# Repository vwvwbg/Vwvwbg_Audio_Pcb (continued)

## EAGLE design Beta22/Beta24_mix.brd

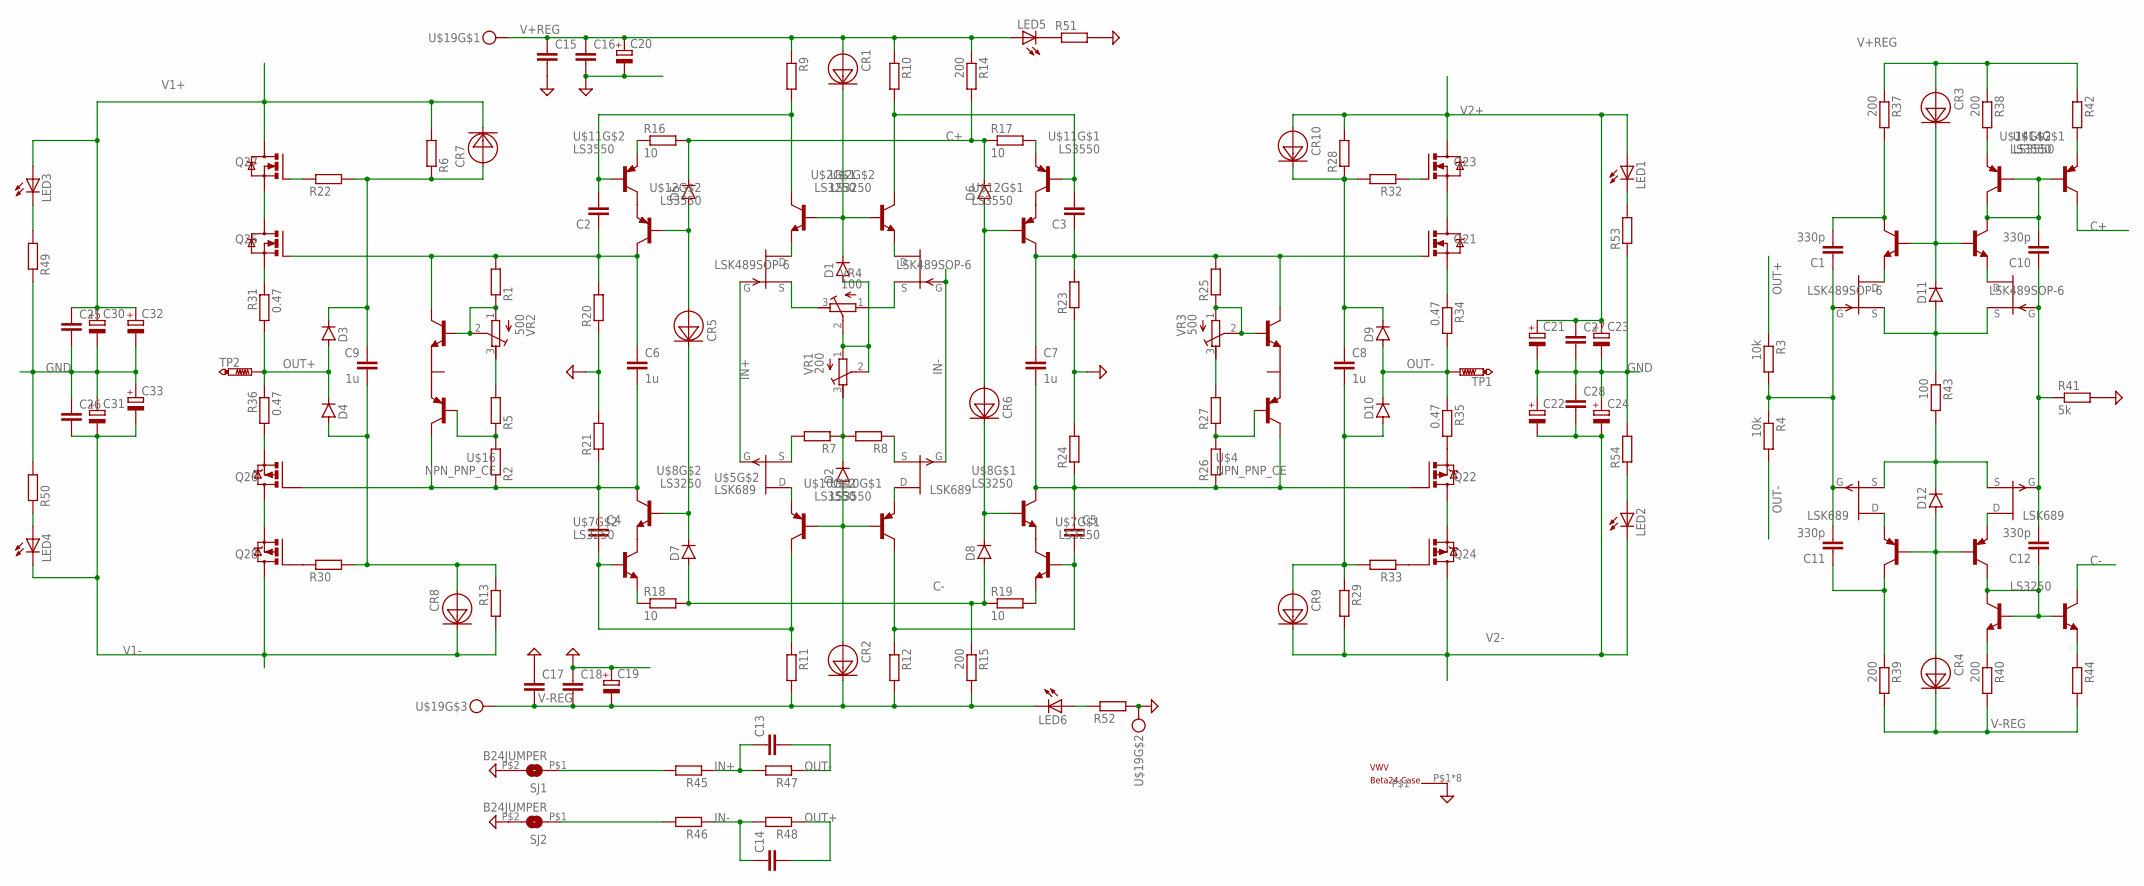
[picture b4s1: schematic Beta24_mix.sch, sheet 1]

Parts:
C1, C10, C11, C12: 330p; C1206
C2, C3, C4, C5, C13, C14, C15, C16, C17, C18, C25, C26, C27, C28: C-EUC1206; C1206
C6, C7: 1u; C1210
C8, C9: 1u; C1206
C19, C20, C21, C22, C23, C24, C30, C31, C32, C33: CPOL-EUG; PANASONIC_G
CR1, CR2, CR3, CR4, CR5, CR6, CR7, CR8, CR9, CR10: 1N5283; SMD
D1, D2, D3, D4, D5, D6, D7, D8, D9, D10, D11, D12: DIODE-SOD80C; SOD80C
LED1, LED2, LED3, LED4, LED5, LED6: LED_LEDSML1206; LED_SML1206
Q21, Q23, Q25, Q27: IRFZ24ND2PAK; TO254P1054X240-3M
Q22, Q24, Q26, Q28: IRF9Z34D2PAK; TO254P1054X240-3M
R1, R2, R5, R6, R7, R8, R9, R10, R11, R12, R13, R20, R21, R22, R23, R24, R25, R26, R27, R28, R29, R30, R32, R33, R42, R44, R45, R46, R47, R48, R49, R50, R52, R53, R54: R-EU_MELF0204W; MINI_MELF-0204W
R3, R4: 10k; MINI_MELF-0204W
R14, R15, R37, R38, R39, R40, R51: 200; MINI_MELF-0204W
R16, R17, R18, R19: 10; MINI_MELF-0204W
R31, R34, R35, R36: 0.47; R2512
R41: 5k; MINI_MELF-0204W
R43: 100; MINI_MELF-0204W
SJ1, SJ2: B24JUMPER; B24J
TP1, TP2: PTR1PAD1-20; P1-20
U$1, U$3: LSK489SOP-6; SOT-23-6
U$2, U$6, U$7, U$8, U$13: LS3250; SOT-23-6
U$4, U$16: NPN_PNP_CE; SOT25
U$5, U$15: LSK689; SOT-23-6
U$9, U$10, U$11, U$12, U$14: LS3550; SOT-23-6
U$17: VWV
U$18: B24C
U$19: CON-PTSM-3
VR1: 200; RTRIM3296W
VR2, VR3: 500; RTRIM3296W
VR4: 100; RTRIM3296W

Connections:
C+: D5.C, D6.C, R14.2, R16.2, R17.1, U$14.6 (C)
C-: D7.A, D8.A, R15.1, R18.2, R19.1, U$13.6 (C)
GND: C15.2, C16.2, C17.1, C18.1, C19.+, C20.-, C21.-, C22.+, C23.-, C24.+, C25.2, C26.1, C27.2, C28.1, C30.-, C31.+, C32.-, C33.+, R20.1, R21.2, R23.1, R24.2, R41.2, R49.1, R50.2, R51.2, R52.2, R53.1, R54.2, SJ1.P$2 (2), SJ2.P$2 (2), U$18.P$1, U$18.P$2, U$18.P$3, U$18.P$4, U$18.P$5, U$18.P$6, U$18.P$7, U$18.P$8, U$19.P$4; also elsewhere on the board
IN+: C13.1, R45.1, R47.2, U$1.1 (G), U$5.4 (G)
IN-: C14.1, R46.1, R48.2, U$1.4 (G), U$5.1 (G)
unnamed: C12.1, U$9.6 (C), U$13.1 (B), U$13.3 (B), U$13.4 (C)
unnamed: U$1.5 (D), U$2.2 (E)
unnamed: U$1.3 (S), VR4.3 (E)
unnamed: R7.2, U$5.6 (S)
unnamed: U$1.2 (D), U$2.5 (E)
unnamed: U$5.5 (D), U$10.2 (E)
unnamed: U$1.6 (S), VR4.1 (A)
unnamed: D2.C, R7.1, R8.2, VR1.3 (E)
unnamed: R8.1, U$5.3 (S)
unnamed: U$5.2 (D), U$10.5 (E)
unnamed: D1.A, VR1.1 (A), VR1.2 (S), VR4.2 (S)
unnamed: CR2.ANODE, D2.A, U$10.1 (B), U$10.3 (B)
unnamed: C2.2, R9.2, U$2.6 (C), U$11.3 (B)
unnamed: C3.2, R10.2, U$2.4 (C), U$11.1 (B)
unnamed: C3.1, C7.1, Q21.1 (G), R23.2, R25.2, U$4.5 (C1), U$12.6 (C)
unnamed: CR1.CATHODE, D1.C, U$2.1 (B), U$2.3 (B)
unnamed: R40.1, U$13.2 (E)
unnamed: C5.2, R12.1, U$7.1 (B), U$10.6 (C)
unnamed: C1.1, C11.2, R3.2, R4.1, U$3.1 (G), U$15.4 (G)
unnamed: C8.2, CR9.ANODE, D10.A, R29.1, R33.2
unnamed: D12.C, R43.2, U$15.3 (S), U$15.6 (S)
unnamed: D11.A, R43.1, U$3.3 (S), U$3.6 (S)
unnamed: U$11.6 (C), U$12.5 (E)
unnamed: C4.2, R11.1, U$7.3 (B), U$10.4 (C)
unnamed: U$11.4 (C), U$12.2 (E)
unnamed: R38.2, U$14.2 (E)
unnamed: R16.1, U$11.2 (E)
unnamed: R17.2, U$11.5 (E)
unnamed: C10.2, U$6.4 (C), U$14.1 (B), U$14.3 (B), U$14.4 (C)
unnamed: R18.1, U$7.2 (E)
unnamed: R19.2, U$7.5 (E)
unnamed: R45.2, SJ1.P$1 (1)
unnamed: U$3.5 (D), U$6.2 (E)
unnamed: CR4.ANODE, D12.A, U$9.1 (B), U$9.3 (B)
unnamed: C2.1, C6.1, Q25.1 (G), R1.2, R20.2, U$12.4 (C), U$16.5 (C1)
unnamed: C4.1, C6.2, Q26.1 (G), R2.1, R21.1, U$8.4 (C), U$16.4 (C2)
unnamed: U$7.6 (C), U$8.5 (E)
unnamed: U$7.4 (C), U$8.2 (E)
unnamed: R25.1, U$4.1 (B1), VR3.1 (A), VR3.2 (S)
unnamed: C1.2, R37.2, U$6.6 (C)
unnamed: CR5.ANODE, D5.A, U$12.3 (B)
unnamed: CR6.ANODE, D6.A, U$12.1 (B)
unnamed: CR5.CATHODE, D7.C, U$8.3 (B)
unnamed: CR6.CATHODE, D8.C, U$8.1 (B)
unnamed: R26.2, R27.1, U$4.3 (B2)
unnamed: R27.2, VR3.3 (E)
unnamed: C5.1, C7.2, Q22.1 (G), R24.1, R26.1, U$4.4 (C2), U$8.6 (C)
unnamed: R2.2, R5.1, U$16.3 (B2)
unnamed: R44.1, U$13.5 (E)
unnamed: C8.1, CR10.CATHODE, D9.C, R28.1, R32.2
unnamed: Q21.2 (D), Q21.4 (D), Q21.P$1 (D), Q21.P$2 (D), Q21.P$3 (D), Q21.P$4 (D), Q21.P$5 (D), Q21.P$6 (D), Q21.P$7 (D), Q21.P$8 (D), Q21.P$9 (D), Q21.P$10 (D), Q21.P$11 (D), Q21.P$12 (D), Q21.P$13 (D), Q21.P$14 (D), Q21.P$15 (D), Q21.P$16 (D), Q21.P$17 (D), Q21.P$18 (D), Q21.P$19 (D), Q21.P$20 (D), Q21.P$21 (D), Q21.P$22 (D), Q21.P$23 (D), Q21.P$24 (D), Q21.P$25 (D), Q21.P$26 (D), Q21.P$27 (D), Q21.P$28 (D), Q21.P$29 (D), Q21.P$30 (D), Q21.P$31 (D), Q21.P$32 (D), Q21.P$33 (D), Q21.P$34 (D), Q21.P$35 (D), Q21.P$36 (D), Q21.P$37 (D), Q21.P$38 (D), Q21.P$39 (D), Q21.P$40 (D), Q21.P$41 (D), Q21.P$42 (D), Q21.P$43 (D), Q21.P$44 (D), Q21.P$45 (D), Q21.P$46 (D), Q21.P$47 (D), Q21.P$48 (D), Q21.P$49 (D), Q21.P$50 (D), Q21.P$51 (D), Q21.P$52 (D), Q21.P$53 (D), Q21.P$54 (D), Q21.P$55 (D), Q21.P$56 (D), Q21.P$57 (D), Q21.P$58 (D), Q21.P$59 (D), Q21.P$60 (D), Q21.P$61 (D), Q21.P$62 (D), Q21.P$63 (D), Q23.3 (S)
unnamed: Q22.2 (D), Q22.4 (D), Q22.P$1 (D), Q22.P$2 (D), Q22.P$3 (D), Q22.P$4 (D), Q22.P$5 (D), Q22.P$6 (D), Q22.P$7 (D), Q22.P$8 (D), Q22.P$9 (D), Q22.P$10 (D), Q22.P$11 (D), Q22.P$12 (D), Q22.P$13 (D), Q22.P$14 (D), Q22.P$15 (D), Q22.P$16 (D), Q22.P$17 (D), Q22.P$18 (D), Q22.P$19 (D), Q22.P$20 (D), Q22.P$21 (D), Q22.P$22 (D), Q22.P$23 (D), Q22.P$24 (D), Q22.P$25 (D), Q22.P$26 (D), Q22.P$27 (D), Q22.P$28 (D), Q22.P$29 (D), Q22.P$30 (D), Q22.P$31 (D), Q22.P$32 (D), Q22.P$33 (D), Q22.P$34 (D), Q22.P$35 (D), Q22.P$36 (D), Q22.P$37 (D), Q22.P$38 (D), Q22.P$39 (D), Q22.P$40 (D), Q22.P$41 (D), Q22.P$42 (D), Q22.P$43 (D), Q22.P$44 (D), Q22.P$45 (D), Q22.P$46 (D), Q22.P$47 (D), Q22.P$48 (D), Q22.P$49 (D), Q22.P$50 (D), Q22.P$51 (D), Q22.P$52 (D), Q22.P$53 (D), Q22.P$54 (D), Q22.P$55 (D), Q22.P$56 (D), Q22.P$57 (D), Q22.P$58 (D), Q22.P$59 (D), Q22.P$60 (D), Q22.P$61 (D), Q22.P$62 (D), Q22.P$63 (D), Q24.3 (S)
unnamed: Q23.1 (G), R32.1
unnamed: Q24.1 (G), R33.1
unnamed: C9.1, CR7.ANODE, D3.C, R6.1, R22.2
unnamed: Q21.3 (S), R34.1
unnamed: Q22.3 (S), R35.2
unnamed: C9.2, CR8.ANODE, D4.A, R13.1, R30.2
unnamed: Q25.2 (D), Q25.4 (D), Q25.P$1 (D), Q25.P$2 (D), Q25.P$3 (D), Q25.P$4 (D), Q25.P$5 (D), Q25.P$6 (D), Q25.P$7 (D), Q25.P$8 (D), Q25.P$9 (D), Q25.P$10 (D), Q25.P$11 (D), Q25.P$12 (D), Q25.P$13 (D), Q25.P$14 (D), Q25.P$15 (D), Q25.P$16 (D), Q25.P$17 (D), Q25.P$18 (D), Q25.P$19 (D), Q25.P$20 (D), Q25.P$21 (D), Q25.P$22 (D), Q25.P$23 (D), Q25.P$24 (D), Q25.P$25 (D), Q25.P$26 (D), Q25.P$27 (D), Q25.P$28 (D), Q25.P$29 (D), Q25.P$30 (D), Q25.P$31 (D), Q25.P$32 (D), Q25.P$33 (D), Q25.P$34 (D), Q25.P$35 (D), Q25.P$36 (D), Q25.P$37 (D), Q25.P$38 (D), Q25.P$39 (D), Q25.P$40 (D), Q25.P$41 (D), Q25.P$42 (D), Q25.P$43 (D), Q25.P$44 (D), Q25.P$45 (D), Q25.P$46 (D), Q25.P$47 (D), Q25.P$48 (D), Q25.P$49 (D), Q25.P$50 (D), Q25.P$51 (D), Q25.P$52 (D), Q25.P$53 (D), Q25.P$54 (D), Q25.P$55 (D), Q25.P$56 (D), Q25.P$57 (D), Q25.P$58 (D), Q25.P$59 (D), Q25.P$60 (D), Q25.P$61 (D), Q25.P$62 (D), Q25.P$63 (D), Q27.3 (S)
unnamed: Q26.2 (D), Q26.4 (D), Q26.P$1 (D), Q26.P$2 (D), Q26.P$3 (D), Q26.P$4 (D), Q26.P$5 (D), Q26.P$6 (D), Q26.P$7 (D), Q26.P$8 (D), Q26.P$9 (D), Q26.P$10 (D), Q26.P$11 (D), Q26.P$12 (D), Q26.P$13 (D), Q26.P$14 (D), Q26.P$15 (D), Q26.P$16 (D), Q26.P$17 (D), Q26.P$18 (D), Q26.P$19 (D), Q26.P$20 (D), Q26.P$21 (D), Q26.P$22 (D), Q26.P$23 (D), Q26.P$24 (D), Q26.P$25 (D), Q26.P$26 (D), Q26.P$27 (D), Q26.P$28 (D), Q26.P$29 (D), Q26.P$30 (D), Q26.P$31 (D), Q26.P$32 (D), Q26.P$33 (D), Q26.P$34 (D), Q26.P$35 (D), Q26.P$36 (D), Q26.P$37 (D), Q26.P$38 (D), Q26.P$39 (D), Q26.P$40 (D), Q26.P$41 (D), Q26.P$42 (D), Q26.P$43 (D), Q26.P$44 (D), Q26.P$45 (D), Q26.P$46 (D), Q26.P$47 (D), Q26.P$48 (D), Q26.P$49 (D), Q26.P$50 (D), Q26.P$51 (D), Q26.P$52 (D), Q26.P$53 (D), Q26.P$54 (D), Q26.P$55 (D), Q26.P$56 (D), Q26.P$57 (D), Q26.P$58 (D), Q26.P$59 (D), Q26.P$60 (D), Q26.P$61 (D), Q26.P$62 (D), Q26.P$63 (D), Q28.3 (S)
unnamed: Q27.1 (G), R22.1
unnamed: Q28.1 (G), R30.1
unnamed: Q26.3 (S), R36.2
unnamed: Q25.3 (S), R31.1
unnamed: R1.1, U$16.1 (B1), VR2.1 (A), VR2.2 (S)
unnamed: R5.2, VR2.3 (E)
unnamed: CR3.CATHODE, D11.C, U$6.1 (B), U$6.3 (B)
unnamed: U$3.2 (D), U$6.5 (E)
unnamed: C10.1, C12.2, R41.1, U$3.4 (G), U$15.1 (G)
unnamed: U$9.2 (E), U$15.5 (D)
unnamed: U$9.5 (E), U$15.2 (D)
unnamed: C11.1, R39.1, U$9.4 (C)
unnamed: R42.2, U$14.5 (E)
unnamed: R46.2, SJ2.P$1 (1)
unnamed: LED3.C, R49.2
unnamed: LED4.A, R50.1
unnamed: LED5.C, R51.1
unnamed: LED6.A, R52.1
unnamed: LED2.A, R54.1
unnamed: LED1.C, R53.2
OUT+: C14.2, D3.A, D4.C, R3.1, R31.2, R36.1, R48.1, TP2.TP
OUT-: C13.2, D9.A, D10.C, R4.2, R34.2, R35.1, R47.1, TP1.TP
V1+: C25.1, C30.+, C32.+, CR7.CATHODE, LED3.A, Q27.2 (D), Q27.4 (D), Q27.P$1 (D), Q27.P$2 (D), Q27.P$3 (D), Q27.P$4 (D), Q27.P$5 (D), Q27.P$6 (D), Q27.P$7 (D), Q27.P$8 (D), Q27.P$9 (D), Q27.P$10 (D), Q27.P$11 (D), Q27.P$12 (D), Q27.P$13 (D), Q27.P$14 (D), Q27.P$15 (D), Q27.P$16 (D), Q27.P$17 (D), Q27.P$18 (D), Q27.P$19 (D), Q27.P$20 (D), Q27.P$21 (D), Q27.P$22 (D), Q27.P$23 (D), Q27.P$24 (D), Q27.P$25 (D), Q27.P$26 (D), Q27.P$27 (D), Q27.P$28 (D), Q27.P$29 (D), Q27.P$30 (D), Q27.P$31 (D), Q27.P$32 (D), Q27.P$33 (D), Q27.P$34 (D), Q27.P$35 (D), Q27.P$36 (D), Q27.P$37 (D), Q27.P$38 (D), Q27.P$39 (D), Q27.P$40 (D), Q27.P$41 (D), Q27.P$42 (D), Q27.P$43 (D), Q27.P$44 (D), Q27.P$45 (D), Q27.P$46 (D), Q27.P$47 (D), Q27.P$48 (D), Q27.P$49 (D), Q27.P$50 (D), Q27.P$51 (D), Q27.P$52 (D), Q27.P$53 (D), Q27.P$54 (D), Q27.P$55 (D), Q27.P$56 (D), Q27.P$57 (D), Q27.P$58 (D), Q27.P$59 (D), Q27.P$60 (D), Q27.P$61 (D), Q27.P$62 (D), Q27.P$63 (D), R6.2; also elsewhere on the board
V1-: C26.2, C31.-, C33.-, CR8.CATHODE, LED4.C, Q28.2 (D), Q28.4 (D), Q28.P$1 (D), Q28.P$2 (D), Q28.P$3 (D), Q28.P$4 (D), Q28.P$5 (D), Q28.P$6 (D), Q28.P$7 (D), Q28.P$8 (D), Q28.P$9 (D), Q28.P$10 (D), Q28.P$11 (D), Q28.P$12 (D), Q28.P$13 (D), Q28.P$14 (D), Q28.P$15 (D), Q28.P$16 (D), Q28.P$17 (D), Q28.P$18 (D), Q28.P$19 (D), Q28.P$20 (D), Q28.P$21 (D), Q28.P$22 (D), Q28.P$23 (D), Q28.P$24 (D), Q28.P$25 (D), Q28.P$26 (D), Q28.P$27 (D), Q28.P$28 (D), Q28.P$29 (D), Q28.P$30 (D), Q28.P$31 (D), Q28.P$32 (D), Q28.P$33 (D), Q28.P$34 (D), Q28.P$35 (D), Q28.P$36 (D), Q28.P$37 (D), Q28.P$38 (D), Q28.P$39 (D), Q28.P$40 (D), Q28.P$41 (D), Q28.P$42 (D), Q28.P$43 (D), Q28.P$44 (D), Q28.P$45 (D), Q28.P$46 (D), Q28.P$47 (D), Q28.P$48 (D), Q28.P$49 (D), Q28.P$50 (D), Q28.P$51 (D), Q28.P$52 (D), Q28.P$53 (D), Q28.P$54 (D), Q28.P$55 (D), Q28.P$56 (D), Q28.P$57 (D), Q28.P$58 (D), Q28.P$59 (D), Q28.P$60 (D), Q28.P$61 (D), Q28.P$62 (D), Q28.P$63 (D), R13.2; also elsewhere on the board
V2+: C21.+, C23.+, C27.1, CR10.ANODE, LED1.A, Q23.2 (D), Q23.4 (D), Q23.P$1 (D), Q23.P$2 (D), Q23.P$3 (D), Q23.P$4 (D), Q23.P$5 (D), Q23.P$6 (D), Q23.P$7 (D), Q23.P$8 (D), Q23.P$9 (D), Q23.P$10 (D), Q23.P$11 (D), Q23.P$12 (D), Q23.P$13 (D), Q23.P$14 (D), Q23.P$15 (D), Q23.P$16 (D), Q23.P$17 (D), Q23.P$18 (D), Q23.P$19 (D), Q23.P$20 (D), Q23.P$21 (D), Q23.P$22 (D), Q23.P$23 (D), Q23.P$24 (D), Q23.P$25 (D), Q23.P$26 (D), Q23.P$27 (D), Q23.P$28 (D), Q23.P$29 (D), Q23.P$30 (D), Q23.P$31 (D), Q23.P$32 (D), Q23.P$33 (D), Q23.P$34 (D), Q23.P$35 (D), Q23.P$36 (D), Q23.P$37 (D), Q23.P$38 (D), Q23.P$39 (D), Q23.P$40 (D), Q23.P$41 (D), Q23.P$42 (D), Q23.P$43 (D), Q23.P$44 (D), Q23.P$45 (D), Q23.P$46 (D), Q23.P$47 (D), Q23.P$48 (D), Q23.P$49 (D), Q23.P$50 (D), Q23.P$51 (D), Q23.P$52 (D), Q23.P$53 (D), Q23.P$54 (D), Q23.P$55 (D), Q23.P$56 (D), Q23.P$57 (D), Q23.P$58 (D), Q23.P$59 (D), Q23.P$60 (D), Q23.P$61 (D), Q23.P$62 (D), Q23.P$63 (D), R28.2; also elsewhere on the board
V2-: C22.-, C24.-, C28.2, CR9.CATHODE, LED2.C, Q24.2 (D), Q24.4 (D), Q24.P$1 (D), Q24.P$2 (D), Q24.P$3 (D), Q24.P$4 (D), Q24.P$5 (D), Q24.P$6 (D), Q24.P$7 (D), Q24.P$8 (D), Q24.P$9 (D), Q24.P$10 (D), Q24.P$11 (D), Q24.P$12 (D), Q24.P$13 (D), Q24.P$14 (D), Q24.P$15 (D), Q24.P$16 (D), Q24.P$17 (D), Q24.P$18 (D), Q24.P$19 (D), Q24.P$20 (D), Q24.P$21 (D), Q24.P$22 (D), Q24.P$23 (D), Q24.P$24 (D), Q24.P$25 (D), Q24.P$26 (D), Q24.P$27 (D), Q24.P$28 (D), Q24.P$29 (D), Q24.P$30 (D), Q24.P$31 (D), Q24.P$32 (D), Q24.P$33 (D), Q24.P$34 (D), Q24.P$35 (D), Q24.P$36 (D), Q24.P$37 (D), Q24.P$38 (D), Q24.P$39 (D), Q24.P$40 (D), Q24.P$41 (D), Q24.P$42 (D), Q24.P$43 (D), Q24.P$44 (D), Q24.P$45 (D), Q24.P$46 (D), Q24.P$47 (D), Q24.P$48 (D), Q24.P$49 (D), Q24.P$50 (D), Q24.P$51 (D), Q24.P$52 (D), Q24.P$53 (D), Q24.P$54 (D), Q24.P$55 (D), Q24.P$56 (D), Q24.P$57 (D), Q24.P$58 (D), Q24.P$59 (D), Q24.P$60 (D), Q24.P$61 (D), Q24.P$62 (D), Q24.P$63 (D), R29.2; also elsewhere on the board
V+REG: C15.1, C16.1, C20.+, CR1.ANODE, CR3.ANODE, LED5.A, R9.1, R10.1, R14.1, R37.1, R38.1, R42.1, U$19.P$3
V-REG: C17.2, C18.2, C19.-, CR2.CATHODE, CR4.CATHODE, LED6.C, R11.2, R12.2, R15.2, R39.2, R40.2, R44.2, U$19.P$5

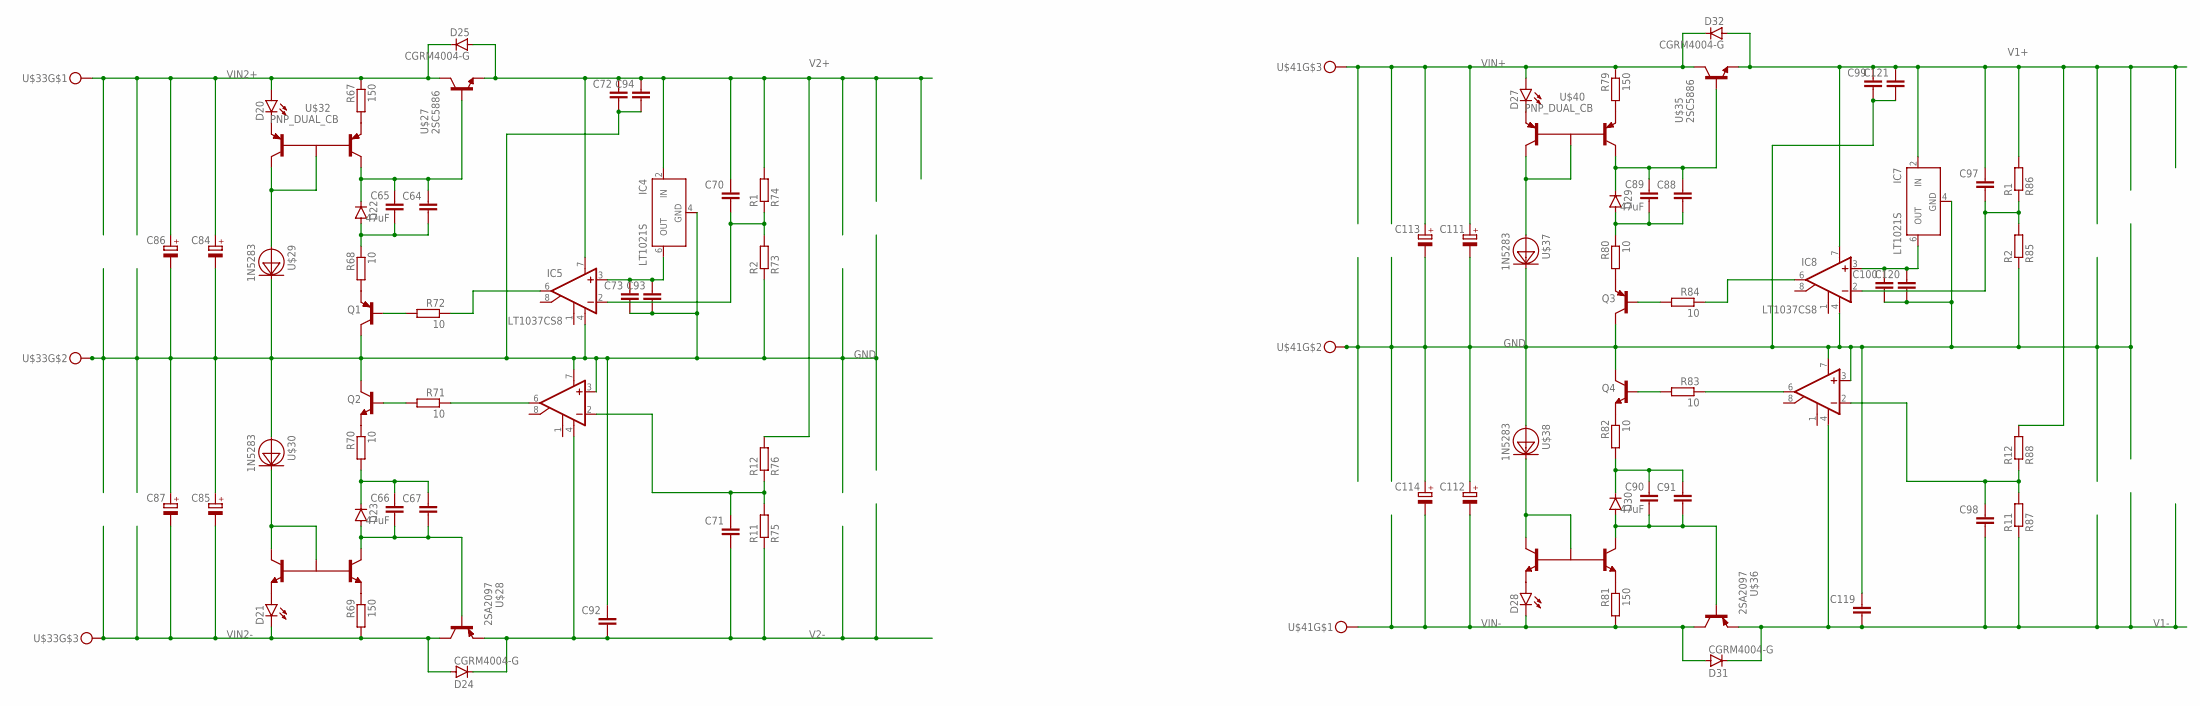
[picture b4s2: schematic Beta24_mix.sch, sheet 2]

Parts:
C64, C67, C70, C71, C72, C73, C88, C91, C92, C93, C94, C97, C98, C99, C100, C119, C120, C121: C-EUC0805; C0805
C65, C66, C89, C90: 47uF; C1206
C84, C85, C86, C87, C111, C112, C113, C114: CPOL-EUG; PANASONIC_G
D20, D21, D27, D28: LEDVWV1206; LED_SML1206
D22, D29: TZMC10; SOD80C
D23, D30: TZAMC10; SOD80C
D24, D25, D31, D32: CGRM4004-G; SOD-123_MINI-SMA
IC4, IC7: LT1021S; SOIC8
IC5, IC6, IC8, IC9: LT1037CS8; SOIC8
Q1, Q3: TRANSISTOR_BC857C-PNP-SOT23-BEC; TRANSISTOR_SOT23-BEC
Q2, Q4: TRANSISTOR_BC847CLT1-NPN-SOT23-BEC; TRANSISTOR_SOT23-BEC
R67, R69, R79, R81: 150; MINI_MELF-0204W
R68, R70, R71, R72, R80, R82, R83, R84: 10; MINI_MELF-0204W
R73, R85: R2; MINI_MELF-0204W
R74, R86: R1; MINI_MELF-0204W
R75, R87: R11; MINI_MELF-0204W
R76, R88: R12; MINI_MELF-0204W
U$27, U$35: 2SC5886; NEW-PWMOLD
U$28, U$36: 2SA2097; NEW-PWMOLD
U$29, U$30, U$37, U$38: 1N5283; SMD
U$31, U$39: NPN_DUAL_CBSOT-25-5; SOT25
U$32, U$40: PNP_DUAL_CB; SOT25
U$33, U$41: CON-PTSM-3

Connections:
GND: C72.2, C73.2, C84.-, C85.+, C86.-, C87.+, C92.1, C93.2, C94.2, C99.2, C100.2, C111.-, C112.+, C113.-, C114.+, C119.1, C120.2, C121.2, IC4.4 (GND), IC5.4 (V-), IC6.3 (+IN), IC6.7 (V+), IC7.4 (GND), IC8.4 (V-), IC9.3 (+IN), IC9.7 (V+), Q1.C, Q2.C, Q3.C, Q4.C, R73.1, R85.1, U$29.CATHODE, U$30.ANODE, U$33.P$4, U$37.CATHODE, U$38.ANODE, U$41.P$4; also elsewhere on the board
unnamed: U$29.ANODE, U$32.2 (B), U$32.5 (C1)
unnamed: C64.1, C65.1, D22.C, U$27.1 (B), U$32.4 (C2)
unnamed: C64.2, C65.2, D22.A, R68.1
unnamed: Q1.E, R68.2
unnamed: Q2.E, R70.1
unnamed: C66.1, C67.1, D23.C, R70.2
unnamed: C66.2, C67.2, D23.A, U$28.1 (B), U$31.4 (C2)
unnamed: U$30.CATHODE, U$31.2 (B), U$31.5 (C1)
unnamed: Q2.B, R71.2
unnamed: Q1.B, R72.2
unnamed: C70.2, IC5.2 (-IN), R73.2, R74.1
unnamed: IC6.6 (OUT), R71.1
unnamed: C71.1, IC6.2 (-IN), R75.2, R76.1
unnamed: C73.1, C93.1, IC4.6 (OUT), IC5.3 (+IN)
unnamed: IC5.6 (OUT), R72.1
unnamed: R69.1, U$31.3 (E2)
unnamed: D21.A, U$31.1 (E1)
unnamed: R67.2, U$32.3 (E2)
unnamed: D20.C, U$32.1 (E1)
unnamed: U$37.ANODE, U$40.2 (B), U$40.5 (C1)
unnamed: C88.1, C89.1, D29.C, U$35.1 (B), U$40.4 (C2)
unnamed: C88.2, C89.2, D29.A, R80.1
unnamed: Q3.E, R80.2
unnamed: Q4.E, R82.1
unnamed: C90.1, C91.1, D30.C, R82.2
unnamed: C90.2, C91.2, D30.A, U$36.1 (B), U$39.4 (C2)
unnamed: U$38.CATHODE, U$39.2 (B), U$39.5 (C1)
unnamed: Q4.B, R83.2
unnamed: Q3.B, R84.2
unnamed: C97.2, IC8.2 (-IN), R85.2, R86.1
unnamed: IC9.6 (OUT), R83.1
unnamed: C98.1, IC9.2 (-IN), R87.2, R88.1
unnamed: C100.1, C120.1, IC7.6 (OUT), IC8.3 (+IN)
unnamed: IC8.6 (OUT), R84.1
unnamed: R81.1, U$39.3 (E2)
unnamed: D28.A, U$39.1 (E1)
unnamed: R79.2, U$40.3 (E2)
unnamed: D27.C, U$40.1 (E1)
V1+: C97.1, C99.1, C121.1, D32.A, IC7.2 (IN), IC8.7 (V+), R86.2, R88.2, U$35.3 (E); also elsewhere on the board
V1-: C98.2, C119.2, D31.C, IC9.4 (V-), R87.1, U$36.3 (E); also elsewhere on the board
V2+: C70.1, C72.1, C94.1, D25.A, IC4.2 (IN), IC5.7 (V+), R74.2, R76.2, U$27.3 (E); also elsewhere on the board
V2-: C71.2, C92.2, D24.C, IC6.4 (V-), R75.1, U$28.3 (E); also elsewhere on the board
VIN2+: C84.+, C86.+, D20.A, D25.C, R67.1, U$27.2 (C), U$27.4 (C), U$27.P$1 (C), U$27.P$2 (C), U$27.P$3 (C), U$27.P$4 (C), U$27.P$5 (C), U$27.P$6 (C), U$27.P$7 (C), U$27.P$8 (C), U$27.P$9 (C), U$27.P$10 (C), U$27.P$11 (C), U$27.P$12 (C), U$27.P$13 (C), U$27.P$14 (C), U$27.P$15 (C), U$27.P$16 (C), U$27.P$17 (C), U$27.P$18 (C), U$27.P$19 (C), U$27.P$20 (C), U$27.P$21 (C), U$27.P$22 (C), U$27.P$23 (C), U$27.P$24 (C), U$27.P$25 (C), U$27.P$26 (C), U$27.P$27 (C), U$27.P$28 (C), U$27.P$29 (C), U$27.P$30 (C), U$27.P$31 (C), U$27.P$32 (C), U$27.P$33 (C), U$27.P$34 (C), U$27.P$35 (C), U$27.P$36 (C), U$27.P$37 (C), U$27.P$38 (C), U$27.P$39 (C), U$27.P$40 (C), U$27.P$41 (C), U$27.P$42 (C), U$27.P$43 (C), U$27.P$44 (C), U$27.P$45 (C), U$27.P$46 (C), U$27.P$47 (C), U$27.P$48 (C), U$27.P$49 (C), U$27.P$50 (C), U$27.P$51 (C), U$27.P$52 (C), U$27.P$53 (C), U$27.P$54 (C), U$27.P$55 (C), U$27.P$56 (C), U$27.P$57 (C), U$27.P$58 (C), U$27.P$59 (C), U$27.P$60 (C), U$27.P$61 (C), U$27.P$62 (C), U$27.P$63 (C), U$33.P$3
VIN2-: C85.-, C87.-, D21.C, D24.A, R69.2, U$28.2 (C), U$28.4 (C), U$28.P$1 (C), U$28.P$2 (C), U$28.P$3 (C), U$28.P$4 (C), U$28.P$5 (C), U$28.P$6 (C), U$28.P$7 (C), U$28.P$8 (C), U$28.P$9 (C), U$28.P$10 (C), U$28.P$11 (C), U$28.P$12 (C), U$28.P$13 (C), U$28.P$14 (C), U$28.P$15 (C), U$28.P$16 (C), U$28.P$17 (C), U$28.P$18 (C), U$28.P$19 (C), U$28.P$20 (C), U$28.P$21 (C), U$28.P$22 (C), U$28.P$23 (C), U$28.P$24 (C), U$28.P$25 (C), U$28.P$26 (C), U$28.P$27 (C), U$28.P$28 (C), U$28.P$29 (C), U$28.P$30 (C), U$28.P$31 (C), U$28.P$32 (C), U$28.P$33 (C), U$28.P$34 (C), U$28.P$35 (C), U$28.P$36 (C), U$28.P$37 (C), U$28.P$38 (C), U$28.P$39 (C), U$28.P$40 (C), U$28.P$41 (C), U$28.P$42 (C), U$28.P$43 (C), U$28.P$44 (C), U$28.P$45 (C), U$28.P$46 (C), U$28.P$47 (C), U$28.P$48 (C), U$28.P$49 (C), U$28.P$50 (C), U$28.P$51 (C), U$28.P$52 (C), U$28.P$53 (C), U$28.P$54 (C), U$28.P$55 (C), U$28.P$56 (C), U$28.P$57 (C), U$28.P$58 (C), U$28.P$59 (C), U$28.P$60 (C), U$28.P$61 (C), U$28.P$62 (C), U$28.P$63 (C), U$33.P$5
VIN+: C111.+, C113.+, D27.A, D32.C, R79.1, U$35.2 (C), U$35.4 (C), U$35.P$1 (C), U$35.P$2 (C), U$35.P$3 (C), U$35.P$4 (C), U$35.P$5 (C), U$35.P$6 (C), U$35.P$7 (C), U$35.P$8 (C), U$35.P$9 (C), U$35.P$10 (C), U$35.P$11 (C), U$35.P$12 (C), U$35.P$13 (C), U$35.P$14 (C), U$35.P$15 (C), U$35.P$16 (C), U$35.P$17 (C), U$35.P$18 (C), U$35.P$19 (C), U$35.P$20 (C), U$35.P$21 (C), U$35.P$22 (C), U$35.P$23 (C), U$35.P$24 (C), U$35.P$25 (C), U$35.P$26 (C), U$35.P$27 (C), U$35.P$28 (C), U$35.P$29 (C), U$35.P$30 (C), U$35.P$31 (C), U$35.P$32 (C), U$35.P$33 (C), U$35.P$34 (C), U$35.P$35 (C), U$35.P$36 (C), U$35.P$37 (C), U$35.P$38 (C), U$35.P$39 (C), U$35.P$40 (C), U$35.P$41 (C), U$35.P$42 (C), U$35.P$43 (C), U$35.P$44 (C), U$35.P$45 (C), U$35.P$46 (C), U$35.P$47 (C), U$35.P$48 (C), U$35.P$49 (C), U$35.P$50 (C), U$35.P$51 (C), U$35.P$52 (C), U$35.P$53 (C), U$35.P$54 (C), U$35.P$55 (C), U$35.P$56 (C), U$35.P$57 (C), U$35.P$58 (C), U$35.P$59 (C), U$35.P$60 (C), U$35.P$61 (C), U$35.P$62 (C), U$35.P$63 (C), U$41.P$5
VIN-: C112.-, C114.-, D28.C, D31.A, R81.2, U$36.2 (C), U$36.4 (C), U$36.P$1 (C), U$36.P$2 (C), U$36.P$3 (C), U$36.P$4 (C), U$36.P$5 (C), U$36.P$6 (C), U$36.P$7 (C), U$36.P$8 (C), U$36.P$9 (C), U$36.P$10 (C), U$36.P$11 (C), U$36.P$12 (C), U$36.P$13 (C), U$36.P$14 (C), U$36.P$15 (C), U$36.P$16 (C), U$36.P$17 (C), U$36.P$18 (C), U$36.P$19 (C), U$36.P$20 (C), U$36.P$21 (C), U$36.P$22 (C), U$36.P$23 (C), U$36.P$24 (C), U$36.P$25 (C), U$36.P$26 (C), U$36.P$27 (C), U$36.P$28 (C), U$36.P$29 (C), U$36.P$30 (C), U$36.P$31 (C), U$36.P$32 (C), U$36.P$33 (C), U$36.P$34 (C), U$36.P$35 (C), U$36.P$36 (C), U$36.P$37 (C), U$36.P$38 (C), U$36.P$39 (C), U$36.P$40 (C), U$36.P$41 (C), U$36.P$42 (C), U$36.P$43 (C), U$36.P$44 (C), U$36.P$45 (C), U$36.P$46 (C), U$36.P$47 (C), U$36.P$48 (C), U$36.P$49 (C), U$36.P$50 (C), U$36.P$51 (C), U$36.P$52 (C), U$36.P$53 (C), U$36.P$54 (C), U$36.P$55 (C), U$36.P$56 (C), U$36.P$57 (C), U$36.P$58 (C), U$36.P$59 (C), U$36.P$60 (C), U$36.P$61 (C), U$36.P$62 (C), U$36.P$63 (C), U$41.P$3

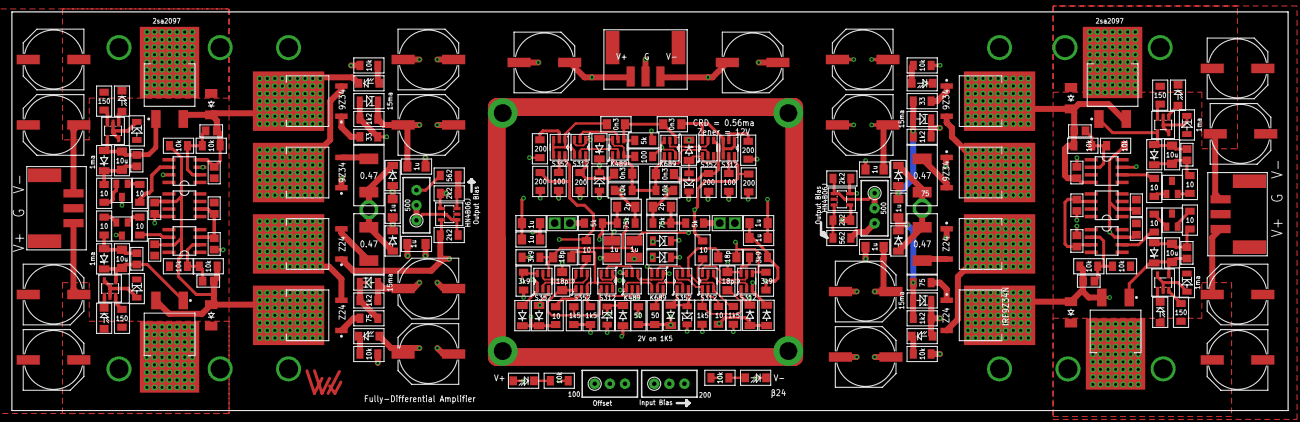
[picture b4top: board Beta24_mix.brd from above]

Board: 4 copper layers, 214.5 x 67.0 mm, 235 parts (0 on the bottom side), 135 nets.

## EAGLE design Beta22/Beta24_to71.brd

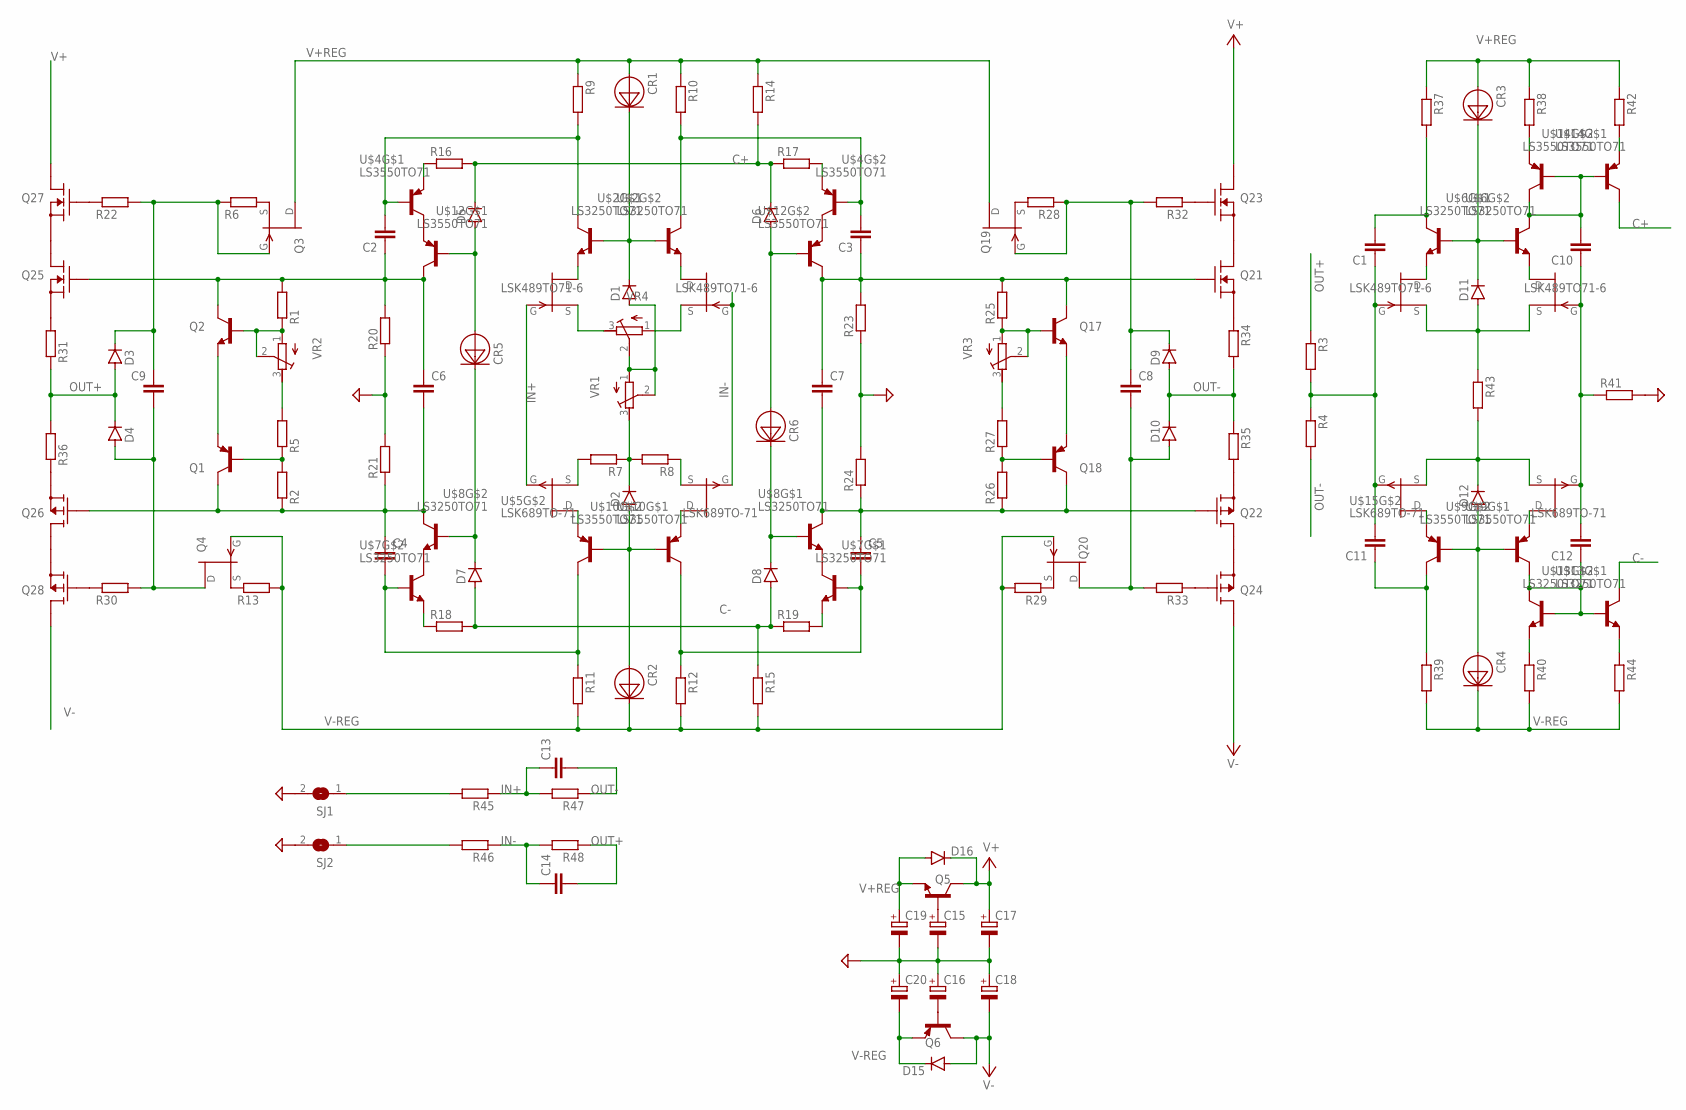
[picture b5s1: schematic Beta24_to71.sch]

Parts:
C1, C2, C3, C4, C5, C6, C7, C8, C9, C10, C11, C12, C13, C14: C-EUC1206; C1206
C15, C16, C19, C20: CPOL-EUE5-13; E5-13
C17, C18: CPOL-EUE7.5-18; E7,5-18
CR1, CR2, CR3, CR4, CR5, CR6: 1N5283; SMD
D1, D2, D3, D4, D5, D6, D7, D8, D9, D10, D11, D12: DIODE-SOD80C; SOD80C
D15, D16: DIODE-SMB; SMB
Q1, Q18: TRANSISTOR_BC858C-PNP-SOT23-BEC; TRANSISTOR_SOT23-BEC
Q2, Q17: TRANSISTOR_BC850-NPN-SOT23-BEC; TRANSISTOR_SOT23-BEC
Q3, Q4, Q19, Q20: 2N4392; TO18
Q5: TRANSISTOR_MMBTA42LT1-NPN-SOT23-BEC; TRANSISTOR_SOT23-BEC
Q6: TRANSISTOR_MMBTA92LT1-PNP-SOT23-BEC; TRANSISTOR_SOT23-BEC
Q21, Q23, Q25, Q27: IRFZ24N; TO220V
Q22, Q24, Q26, Q28: IRFZ34N; TO220V
R1, R2, R3, R4, R5, R6, R7, R8, R9, R10, R11, R12, R13, R14, R15, R16, R17, R18, R19, R20, R21, R22, R23, R24, R25, R26, R27, R28, R29, R30, R32, R33, R37, R38, R39, R40, R41, R42, R43, R44, R45, R46, R47, R48: R-EU_MELF0204W; MINI_MELF-0204W
R31, R34, R35, R36: R-EU_TO220; TO220-2
SJ1, SJ2: SJ
U$1, U$3: LSK489TO71-6; TO71-6
U$2, U$6, U$7, U$8, U$13: LS3250TO71; TO71-6
U$4, U$9, U$10, U$12, U$14: LS3550TO71; TO71-6
U$5, U$15: LSK689TO-71; TO71-6
VR1, VR2, VR3, VR4: R-TRIMM3296W; RTRIM3296W

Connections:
C+: D5.C, D6.C, R14.2, R16.2, R17.1, U$14.1 (C)
C-: D7.A, D8.A, R15.1, R18.2, R19.1, U$13.1 (C)
GND: C15.-, C16.+, C17.-, C18.+, C19.-, C20.+, R20.1, R21.2, R23.1, R24.2, R41.2, SJ1.2, SJ2.2
IN+: C13.1, R45.1, R47.2, U$1.3 (G), U$5.7 (G)
IN-: C14.1, R46.1, R48.2, U$1.7 (G), U$5.3 (G)
unnamed: C12.1, U$9.1 (C), U$13.2 (B), U$13.6 (B), U$13.7 (C)
unnamed: U$1.6 (D), U$2.5 (E)
unnamed: U$1.1 (S), VR4.3 (E)
unnamed: R7.2, U$5.5 (S)
unnamed: U$1.2 (D), U$2.3 (E)
unnamed: U$5.6 (D), U$10.5 (E)
unnamed: U$1.5 (S), VR4.1 (A)
unnamed: D2.C, R7.1, R8.2, VR1.3 (E)
unnamed: R8.1, U$5.1 (S)
unnamed: U$5.2 (D), U$10.3 (E)
unnamed: D1.A, VR1.1 (A), VR1.2 (S), VR4.2 (S)
unnamed: CR2.ANODE, D2.A, U$10.2 (B), U$10.6 (B)
unnamed: C2.2, R9.2, U$2.1 (C), U$4.2 (B)
unnamed: C3.2, R10.2, U$2.7 (C), U$4.6 (B)
unnamed: C3.1, C7.1, Q17.C, Q21.1 (G), R23.2, R25.2, U$12.7 (C)
unnamed: CR1.CATHODE, D1.C, U$2.2 (B), U$2.6 (B)
unnamed: R40.1, U$13.5 (E)
unnamed: C5.2, R12.1, U$7.2 (B), U$10.1 (C)
unnamed: C1.1, C11.2, R3.2, R4.1, U$3.3 (G), U$15.7 (G)
unnamed: C8.2, D10.A, Q20.2 (D), R33.2
unnamed: D12.C, R43.2, U$15.1 (S), U$15.5 (S)
unnamed: D11.A, R43.1, U$3.1 (S), U$3.5 (S)
unnamed: U$4.1 (C), U$12.3 (E)
unnamed: C4.2, R11.1, U$7.6 (B), U$10.7 (C)
unnamed: U$4.7 (C), U$12.5 (E)
unnamed: R38.2, U$14.5 (E)
unnamed: R16.1, U$4.3 (E)
unnamed: R17.2, U$4.5 (E)
unnamed: C10.2, U$6.7 (C), U$14.2 (B), U$14.6 (B), U$14.7 (C)
unnamed: R18.1, U$7.5 (E)
unnamed: R19.2, U$7.3 (E)
unnamed: R45.2, SJ1.1
unnamed: U$3.6 (D), U$6.5 (E)
unnamed: CR4.ANODE, D12.A, U$9.2 (B), U$9.6 (B)
unnamed: C2.1, C6.1, Q2.C, Q25.1 (G), R1.2, R20.2, U$12.1 (C)
unnamed: C4.1, C6.2, Q1.C, Q26.1 (G), R2.1, R21.1, U$8.7 (C)
unnamed: U$7.1 (C), U$8.3 (E)
unnamed: U$7.7 (C), U$8.5 (E)
unnamed: Q17.B, R25.1, VR3.1 (A), VR3.2 (S)
unnamed: Q19.1 (S), R28.2
unnamed: Q20.1 (S), R29.1
unnamed: C1.2, R37.2, U$6.1 (C)
unnamed: CR5.ANODE, D5.A, U$12.2 (B)
unnamed: CR6.ANODE, D6.A, U$12.6 (B)
unnamed: CR5.CATHODE, D7.C, U$8.6 (B)
unnamed: CR6.CATHODE, D8.C, U$8.2 (B)
unnamed: Q18.B, R26.2, R27.1
unnamed: R27.2, VR3.3 (E)
unnamed: Q17.E, Q18.E
unnamed: C5.1, C7.2, Q18.C, Q22.1 (G), R24.1, R26.1, U$8.1 (C)
unnamed: Q1.B, R2.2, R5.1
unnamed: Q1.E, Q2.E
unnamed: R44.1, U$13.3 (E)
unnamed: C8.1, D9.C, Q19.3 (G), R28.1, R32.2
unnamed: Q3.1 (S), R6.2
unnamed: Q4.1 (S), R13.1
unnamed: Q21.2 (D), Q23.3 (S)
unnamed: Q22.2 (D), Q24.3 (S)
unnamed: Q23.1 (G), R32.1
unnamed: Q24.1 (G), R33.1
unnamed: C9.1, D3.C, Q3.3 (G), R6.1, R22.2
unnamed: Q21.3 (S), R34.1
unnamed: Q22.3 (S), R35.2
unnamed: C9.2, D4.A, Q4.2 (D), R30.2
unnamed: Q25.2 (D), Q27.3 (S)
unnamed: Q26.2 (D), Q28.3 (S)
unnamed: Q27.1 (G), R22.1
unnamed: Q28.1 (G), R30.1
unnamed: Q25.3 (S), R31.2
unnamed: Q26.3 (S), R36.1
unnamed: Q2.B, R1.1, VR2.1 (A), VR2.2 (S)
unnamed: R5.2, VR2.3 (E)
unnamed: CR3.CATHODE, D11.C, U$6.2 (B), U$6.6 (B)
unnamed: U$3.2 (D), U$6.3 (E)
unnamed: C10.1, C12.2, R41.1, U$3.7 (G), U$15.3 (G)
unnamed: U$9.5 (E), U$15.6 (D)
unnamed: C15.+, Q5.B
unnamed: U$9.3 (E), U$15.2 (D)
unnamed: C11.1, R39.1, U$9.7 (C)
unnamed: R42.2, U$14.3 (E)
unnamed: R46.2, SJ2.1
unnamed: C16.-, Q6.B
OUT+: C14.2, D3.A, D4.C, R3.1, R31.1, R36.2, R48.1
OUT-: C13.2, D9.A, D10.C, R4.2, R34.2, R35.1, R47.1
V+: C17.+, D16.C, Q5.C, Q23.2 (D), Q27.2 (D)
V+REG: C19.+, CR1.ANODE, CR3.ANODE, D16.A, Q3.2 (D), Q5.E, Q19.2 (D), R9.1, R10.1, R14.1, R37.1, R38.1, R42.1
V-: C18.-, D15.A, Q6.C, Q24.2 (D), Q28.2 (D)
V-REG: C20.-, CR2.CATHODE, CR4.CATHODE, D15.C, Q4.3 (G), Q6.E, Q20.3 (G), R11.2, R12.2, R13.2, R15.2, R29.2, R39.2, R40.2, R44.2

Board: 4 copper layers, 126 parts (0 on the bottom side), 93 nets, no tracks yet.
